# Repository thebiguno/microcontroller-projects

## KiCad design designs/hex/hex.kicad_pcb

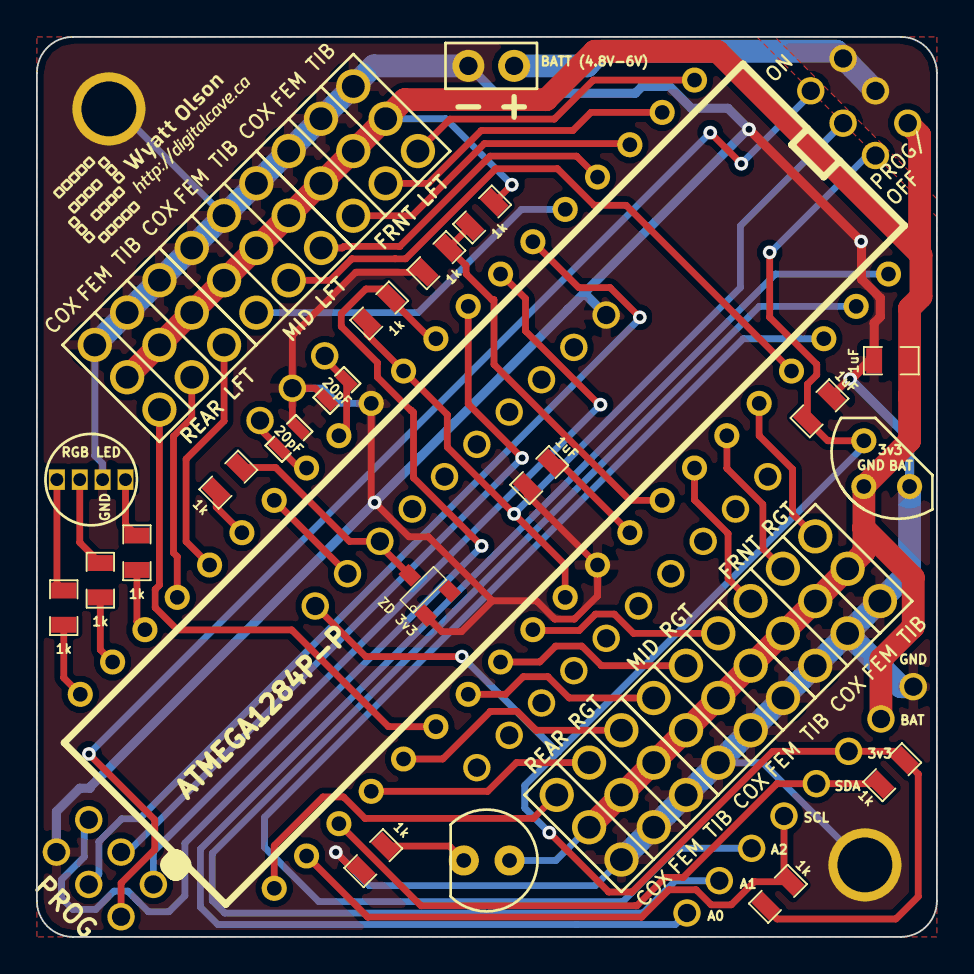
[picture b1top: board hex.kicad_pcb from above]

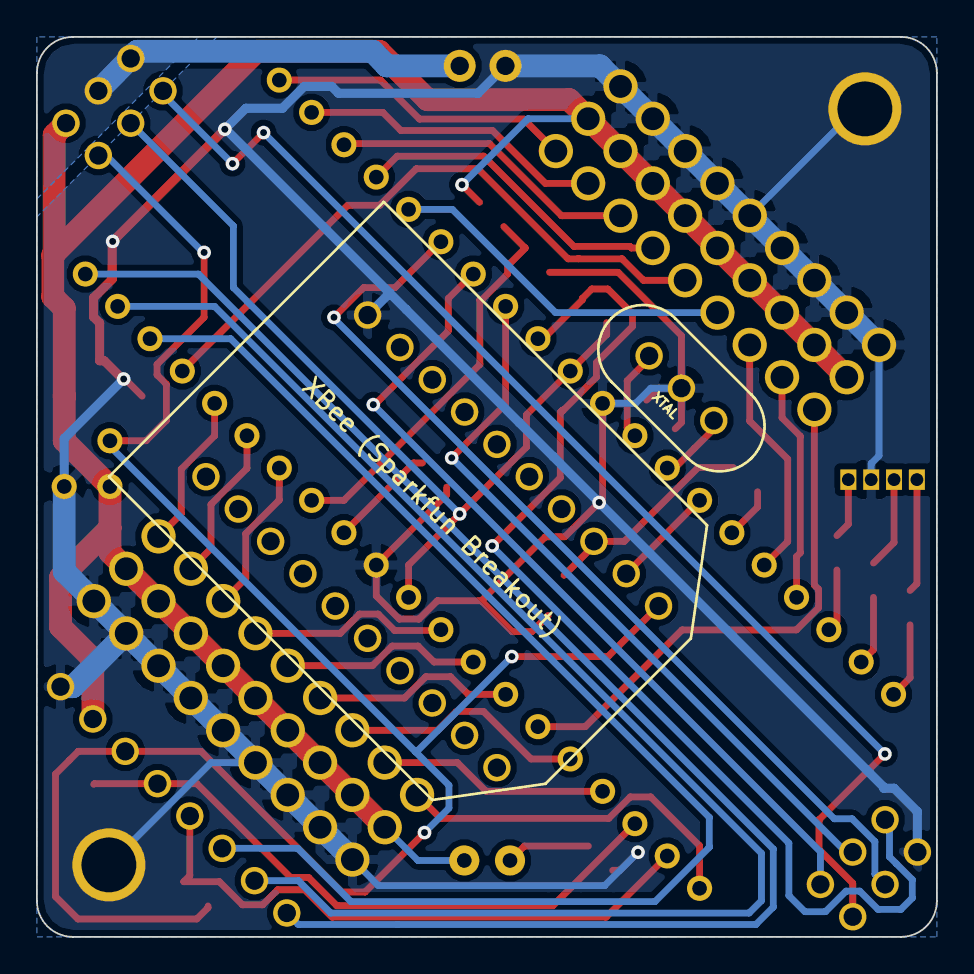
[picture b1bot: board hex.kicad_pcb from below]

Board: 2 copper layers, 50.0 x 50.0 mm, 35 parts (2 on the bottom side), 47 nets.

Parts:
1PIN, 1PIN#2: P***; 1pin
C1, C2, C3: 1uF; SM0805
C4, C5: 20pF; SM0603_Capa
D1: LED; LED-5MM
IC1: ATMEGA1284P-P; DIP-40__600
K1: XTAL; PIN_ARRAY_3X1
K2: REGUL; TO92
L1: RGB LED; LED_RGB
P1: PROG; pin_array_3x2
P2: BATT (4.8V-6V); PIN_ARRAY_2X1
P3: CONN_8; PIN_ARRAY_8x1
R1, R2, R3, R4, R5, R6, R7, R8, R9, R10: 1k; SM0805
S1: FRNT LFT; HEX_LEG
S2: FRNT RGT; HEX_LEG_REVERSE
S3: MID LFT; HEX_LEG
S4: MID RGT; HEX_LEG_REVERSE
S5: REAR LFT; HEX_LEG
S6: REAR RGT; HEX_LEG_REVERSE
SW1: DPDT
VAL: DIGITALCAVE_LOGO_WIDE_SMALL
X1: XBee (Sparkfun Breakout); XBEE_SPARKFUN_BREAKOUT
ZD1: ZD 3v3; SOT23

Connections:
ADC0: IC1.40, P3.1
ADC1: IC1.39, P3.2
ADC2: IC1.38, P3.3
ADC_BATTERY_METER: IC1.33, R2.2, R3.2
AREF: C1.2, IC1.32
AVR_RX: IC1.14, X1.2
AVR_TX: R9.2, X1.3, ZD1.2
BATTERY: P2.1, SW1.1, SW1.2
GND: 1PIN.1, 1PIN#2.1, C1.1, C2.1, C3.2, C4.1, C5.1, IC1.11, IC1.31, K1.2, K2.1, L1.2, P1.6, P2.2, P3.8, R3.1, R10.2, S1.7, S1.8, S1.9, S2.7, S2.8, S2.9, S3.7, S3.8, S3.9, S4.7, S4.8, S4.9, S5.7, S5.8, S5.9, S6.7, S6.8, S6.9, X1.10, ZD1.1
I2C_SCL: IC1.22, P3.4, R8.2
I2C_SDA: IC1.23, P3.5, R7.2
LED_BLUE: IC1.19, R6.1
LED_BLUE_R: L1.3, R6.2
LED_GREEN: IC1.20, R5.1
LED_GREEN_R: L1.4, R5.2
LED_RED: IC1.18, R4.1
LED_RED_R: L1.1, R4.2
MISO: IC1.7, P1.1
MOSI: IC1.6, P1.4
unnamed: D1.2, R10.1
unnamed: IC1.15, R9.1
PWM00: IC1.3, S1.1
PWM01: IC1.2, S1.2
PWM02: IC1.1, S1.3
PWM03: IC1.36, S2.1
PWM04: IC1.35, S2.2
PWM05: IC1.34, S2.3
PWM06: IC1.5, S3.1
PWM07: IC1.37, S3.2
PWM08: IC1.4, S3.3
PWM09: IC1.29, S4.1
PWM10: IC1.28, S4.2
PWM11: IC1.27, S4.3
PWM12: IC1.26, S5.1
PWM13: IC1.17, S5.2
PWM14: IC1.16, S5.3
PWM15: IC1.25, S6.1
PWM16: IC1.24, S6.2
PWM17: IC1.21, S6.3
RESET: IC1.9, P1.5, R1.1
SCK: IC1.8, P1.3
SWITCHED_BATTERY: C2.2, D1.1, K2.2, P3.7, R2.1, S1.4, S1.5, S1.6, S2.4, S2.5, S2.6, S3.4, S3.5, S3.6, S4.4, S4.5, S4.6, S5.4, S5.5, S5.6, S6.4, S6.5, S6.6, SW1.3
VCC_3v3: C3.1, K2.3, P3.6, R7.1, R8.1, SW1.6, X1.1
VCC_AVR: IC1.10, IC1.30, R1.2, SW1.5
VCC_PROG: P1.2, SW1.4
XTAL1: C5.2, IC1.13, K1.1
XTAL2: C4.2, IC1.12, K1.3

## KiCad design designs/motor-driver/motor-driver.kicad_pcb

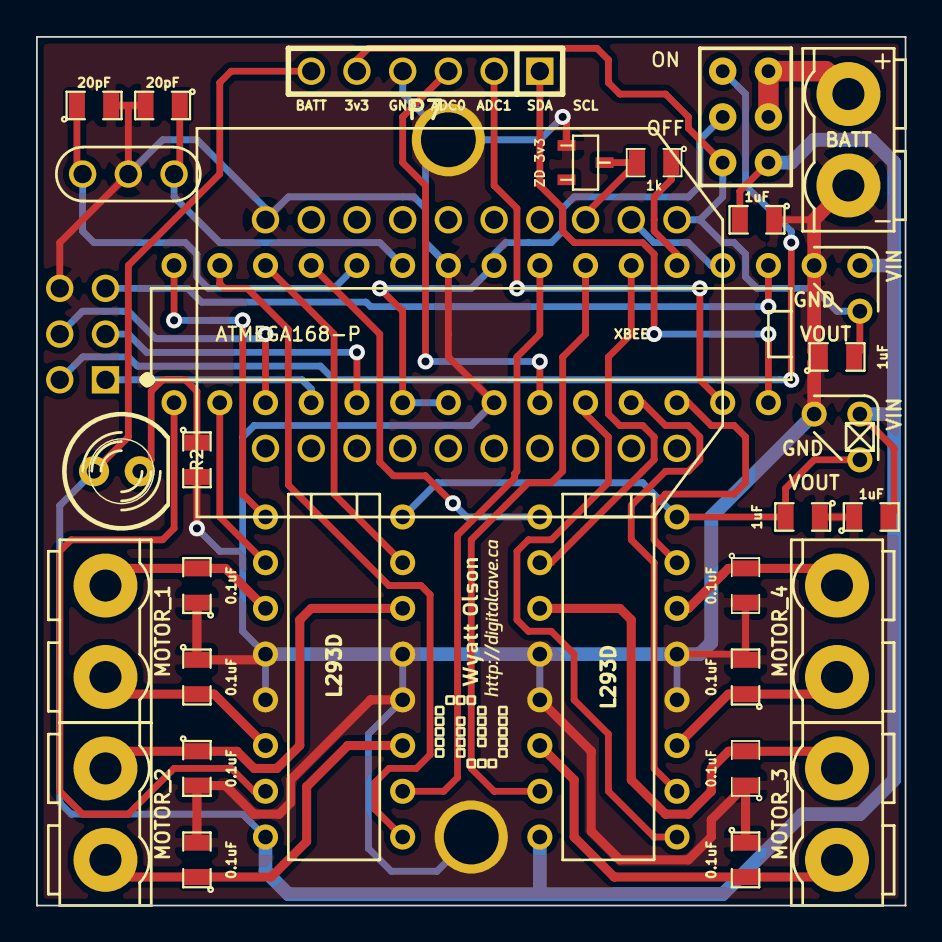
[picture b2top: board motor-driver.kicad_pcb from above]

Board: 2 copper layers, 48.3 x 48.3 mm, 36 parts (0 on the bottom side), 40 nets.

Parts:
1PIN, 1PIN#2: P***; 1pin
C1, C2, C3, C4: 1uF; SM0805
C5, C6: 20pF; SM0805
C7, C8, C9, C10, C11, C12, C13, C14: 0.1uF; SM0805
D1: ZD 3v3; sot23
D2: LED; LED-5MM
IC1: ATMEGA168-P; DIP-28__300
P1: BATT; SCREW_TERMINAL_2
P2: ISP
P3: MOTOR_1; SCREW_TERMINAL_2
P4: MOTOR_2; SCREW_TERMINAL_2
P5: MOTOR_3; SCREW_TERMINAL_2
P6: MOTOR_4; SCREW_TERMINAL_2
P7: CONN_6; PIN_ARRAY-6X1
R1, R2: 1k; SM0805
S1: DPDT
U1, U2: L293D; DIP-16__300
VAL: DIGITALCAVE_LOGO_WIDE_SMALL
VR1, VR2: MCP1702; TO92_SMALL
X1: CRYSTAL_RESONATOR
X2: XBEE; XBEE_SPARKFUN_BREAKOUT

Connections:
+3.3V: C4.2, P7.5, S1.6, VR2.3, X2.1
+5V: C2.2, U1.16, U2.16, VR1.3
+BATT: C1.2, C3.2, D2.1, P7.6, S1.3, U1.8, U2.8, VR1.2, VR2.2
/ADC0: IC1.23, P7.3
/AVR_VCC: IC1.7, IC1.20, IC1.21, S1.5
/BATTERY: P1.2, S1.1, S1.2
/MISO: IC1.18, P2.1
/MOSI: IC1.17, P2.4
/MOTOR1_1A: IC1.16, U1.2
/MOTOR1_1Y: C7.2, P3.1, U1.3
/MOTOR1_2A: IC1.15, U1.7
/MOTOR1_2Y: C11.2, P3.2, U1.6
/MOTOR1_ENABLE: IC1.14, U1.1
/MOTOR2_3A: IC1.6, U1.10
/MOTOR2_3Y: C12.1, P4.2, U1.11
/MOTOR2_4A: IC1.12, U1.15
/MOTOR2_4Y: C8.1, P4.1, U1.14
/MOTOR2_ENABLE: IC1.13, U1.9
/MOTOR3_1A: IC1.4, U2.2
/MOTOR3_1Y: C9.2, P5.2, U2.3
/MOTOR3_2A: IC1.5, U2.7
/MOTOR3_2Y: C13.2, P5.1, U2.6
/MOTOR3_ENABLE: IC1.11, U2.1
/MOTOR4_3A: IC1.25, U2.10
/MOTOR4_3Y: C14.1, P6.1, U2.11
/MOTOR4_4A: IC1.26, U2.15
/MOTOR4_4Y: C10.1, P6.2, U2.14
/MOTOR4_ENABLE: IC1.24, U2.9
/PROG_VCC: P2.2, S1.4
/RESET: IC1.1, P2.5
/RX: IC1.2, X2.2
/SCK: IC1.19, P2.3
/SCL: IC1.28, P7.1
/SDA: IC1.27, P7.2
/TX: IC1.3, R1.1
/XTAL1: C5.1, IC1.9, X1.1
/XTAL2: C6.1, IC1.10, X1.2
GND: 1PIN.1, 1PIN#2.1, C1.1, C2.1, C3.1, C4.1, C5.2, C6.2, C7.1, C8.2, C9.1, C10.2, C11.1, C12.2, C13.1, C14.2, D1.1, IC1.8, IC1.22, P1.1, P2.6, P7.4, R2.2, U1.4, U1.5, U1.12, U1.13, U2.4, U2.5, U2.12, U2.13, VR1.1, VR2.1, X1.3, X2.10
unnamed: D2.2, R2.1
unnamed: D1.2, R1.2, X2.3

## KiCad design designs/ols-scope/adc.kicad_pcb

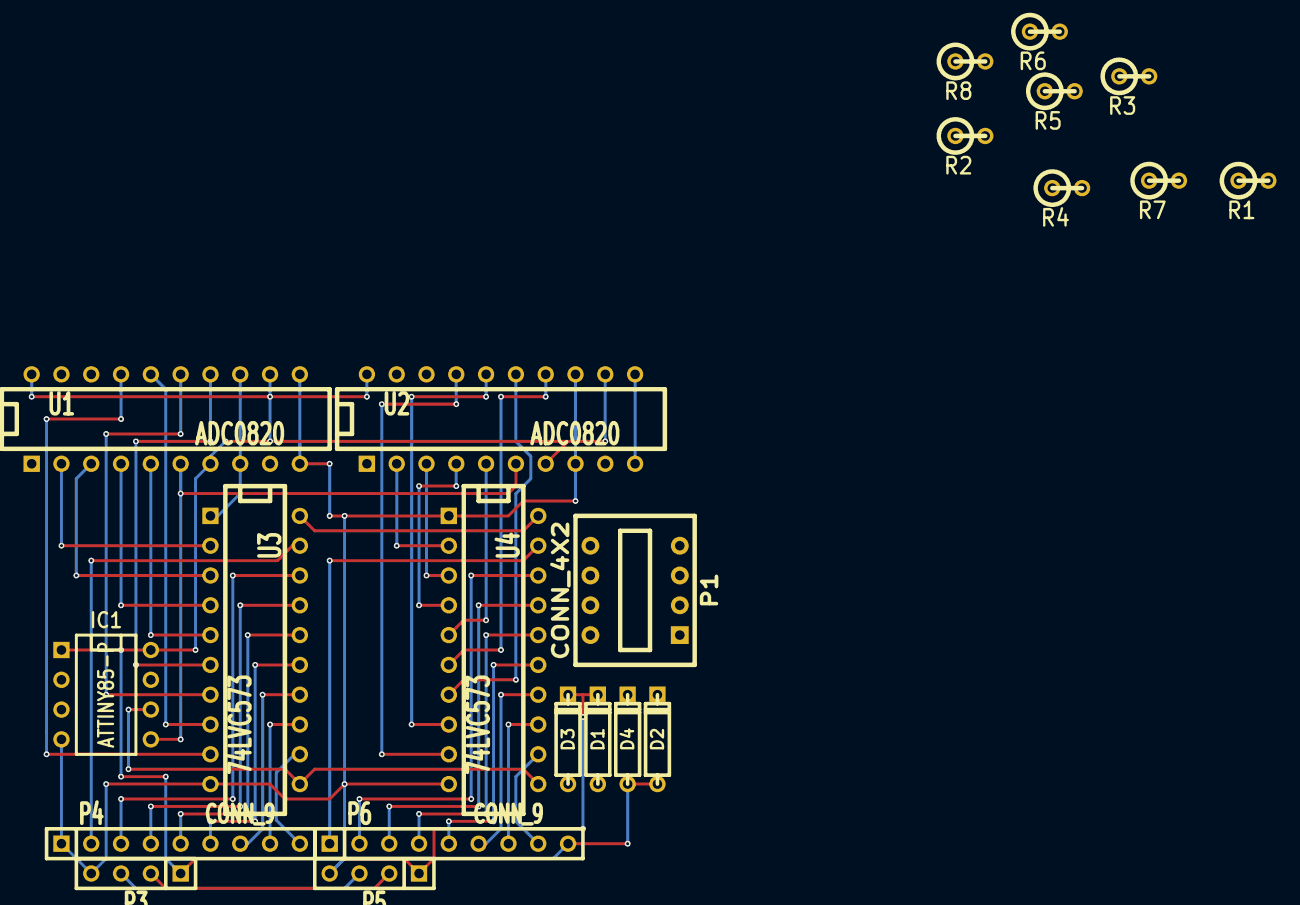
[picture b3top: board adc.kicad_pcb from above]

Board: 2 copper layers, 22 parts (0 on the bottom side), 47 nets.

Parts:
D1, D2, D3, D4: DIODESCH; D3
IC1: ATTINY85-P; DIP-8__300
P1: CONN_4X2; SWDIP4
P3, P5: CONN_4; SIL-4
P4, P6: CONN_9; SIL-9
R1, R2: 1k; R1
R3, R5: 10k; R1
R4, R6: 2k; R1
R7, R8: 100k; R1
U1, U2: ADC0820; DIP-20__300
U3, U4: 74LVC573; DIP-20__300

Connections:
+2.5V: P3.3, P5.3
+3.3V: P3.2, P5.2
+5V: D1.2, D3.2, IC1.1, IC1.8, P3.1, P5.1, U1.7, U1.12, U1.20, U2.7, U2.12, U2.20
ANALOG_IN_1: P1.1, R3.1
ANALOG_IN_2: P1.5, R5.1
Channel 16: P4.2, U3.19
Channel 17: P4.3, U3.18
Channel 18: P4.4, U3.17
Channel 19: P4.5, U3.16
Channel 20: P4.6, U3.15
Channel 21: P4.7, U3.14
Channel 22: P4.8, U3.13
Channel 23: P4.9, U3.12
Channel 24: P6.1, U4.19
Channel 25: P6.2, U4.18
Channel 26: P6.3, U4.17
Channel 27: P6.4, U4.16
Channel 28: P6.5, U4.15
Channel 29: P6.6, U4.14
Channel 30: P6.7, U4.13
Channel 31: P6.8, U4.12
DIP_1B: P1.2, P1.4, R3.2, R4.1
DIP_2A: P1.3, R1.1, R4.2, R7.1
DIP_3B: P1.6, P1.8, R5.2, R6.1
DIP_4A: P1.7, R2.1, R6.2, R8.1
GND: D2.1, D4.1, IC1.4, P3.4, P4.1, P5.4, P6.9, R1.2, R2.2, U1.8, U1.10, U1.11, U1.13, U2.8, U2.10, U2.11, U2.13, U3.1, U3.10, U4.1, U4.10
unnamed: U2.17, U4.9
unnamed: U2.16, U4.8
unnamed: U2.15, U4.7
unnamed: U2.14, U4.6
unnamed: U2.5, U4.5
unnamed: U2.4, U4.4
unnamed: U2.3, U4.3
unnamed: U2.2, U4.2
unnamed: IC1.5, U1.6, U2.6
unnamed: IC1.6, U3.11, U4.11
unnamed: U1.3, U3.3
unnamed: U1.2, U3.2
unnamed: D1.1, D2.2, R7.2, U1.1
unnamed: U1.16, U3.8
unnamed: U1.17, U3.9
unnamed: U1.15, U3.7
unnamed: U1.14, U3.6
unnamed: U1.5, U3.5
unnamed: U1.4, U3.4
unnamed: D3.1, D4.2, R8.2, U2.1
VCC: U3.20, U4.20

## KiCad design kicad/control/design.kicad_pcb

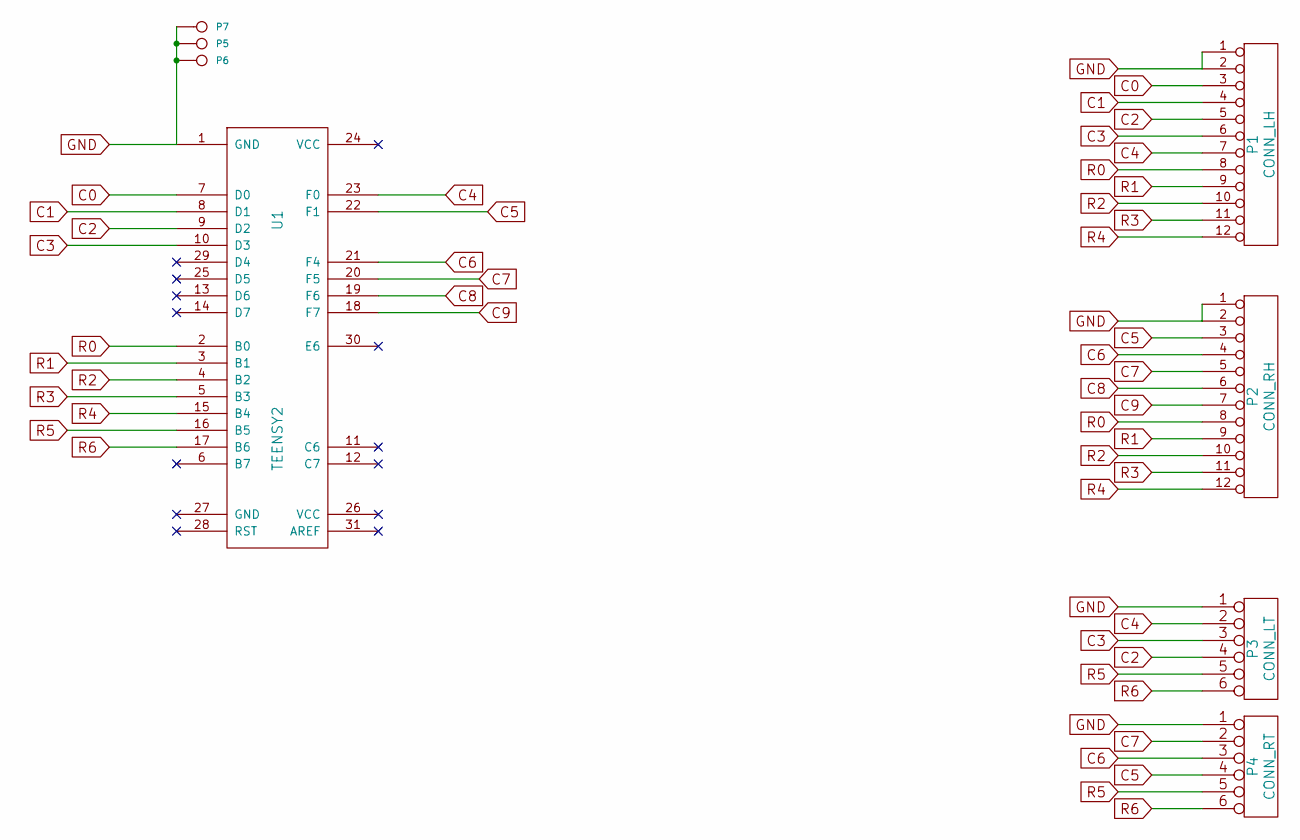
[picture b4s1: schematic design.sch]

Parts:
P1: CONN_LH
P2: CONN_RH
P3: CONN_LT
P4: CONN_RT
P5, P6, P7: CONN_1
U1: TEENSY2

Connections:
C0: P1.3, U1.7 (D0)
C1: P1.4, U1.8 (D1)
C2: P1.5, P3.4, U1.9 (D2)
C3: P1.6, P3.3, U1.10 (D3)
C4: P1.7, P3.2, U1.23 (F0)
C5: P2.3, P4.4, U1.22 (F1)
C6: P2.4, P4.3, U1.21 (F4)
C7: P2.5, P4.2, U1.20 (F5)
C8: P2.6, U1.19 (F6)
C9: P2.7, U1.18 (F7)
GND: P1.1, P1.2, P2.1, P2.2, P3.1, P4.1, P5.1, P6.1, P7.1, U1.1 (GND)
R0: P1.8, P2.8, U1.2 (B0)
R1: P1.9, P2.9, U1.3 (B1)
R2: P1.10, P2.10, U1.4 (B2)
R3: P1.11, P2.11, U1.5 (B3)
R4: P1.12, P2.12, U1.15 (B4)
R5: P3.5, P4.5, U1.16 (B5)
R6: P3.6, P4.6, U1.17 (B6)

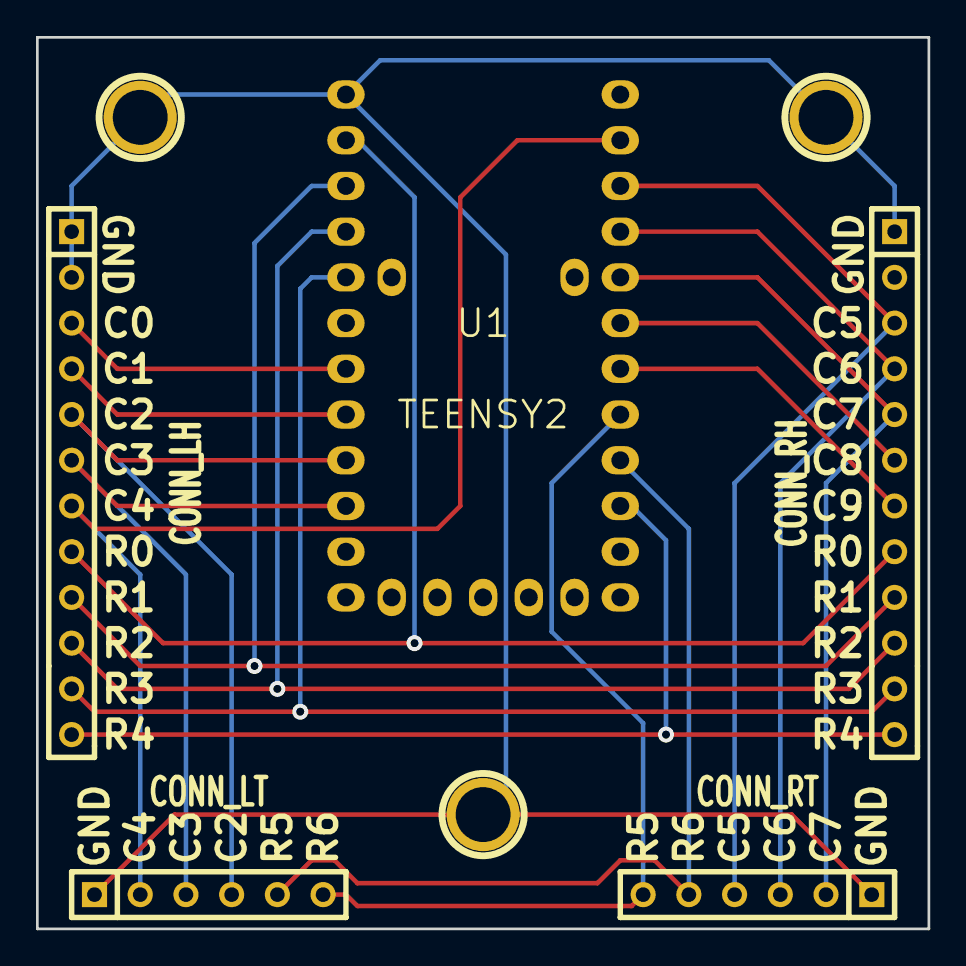
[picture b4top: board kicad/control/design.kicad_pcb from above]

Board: 2 copper layers, 49.5 x 49.5 mm, 8 parts (0 on the bottom side), 18 nets.

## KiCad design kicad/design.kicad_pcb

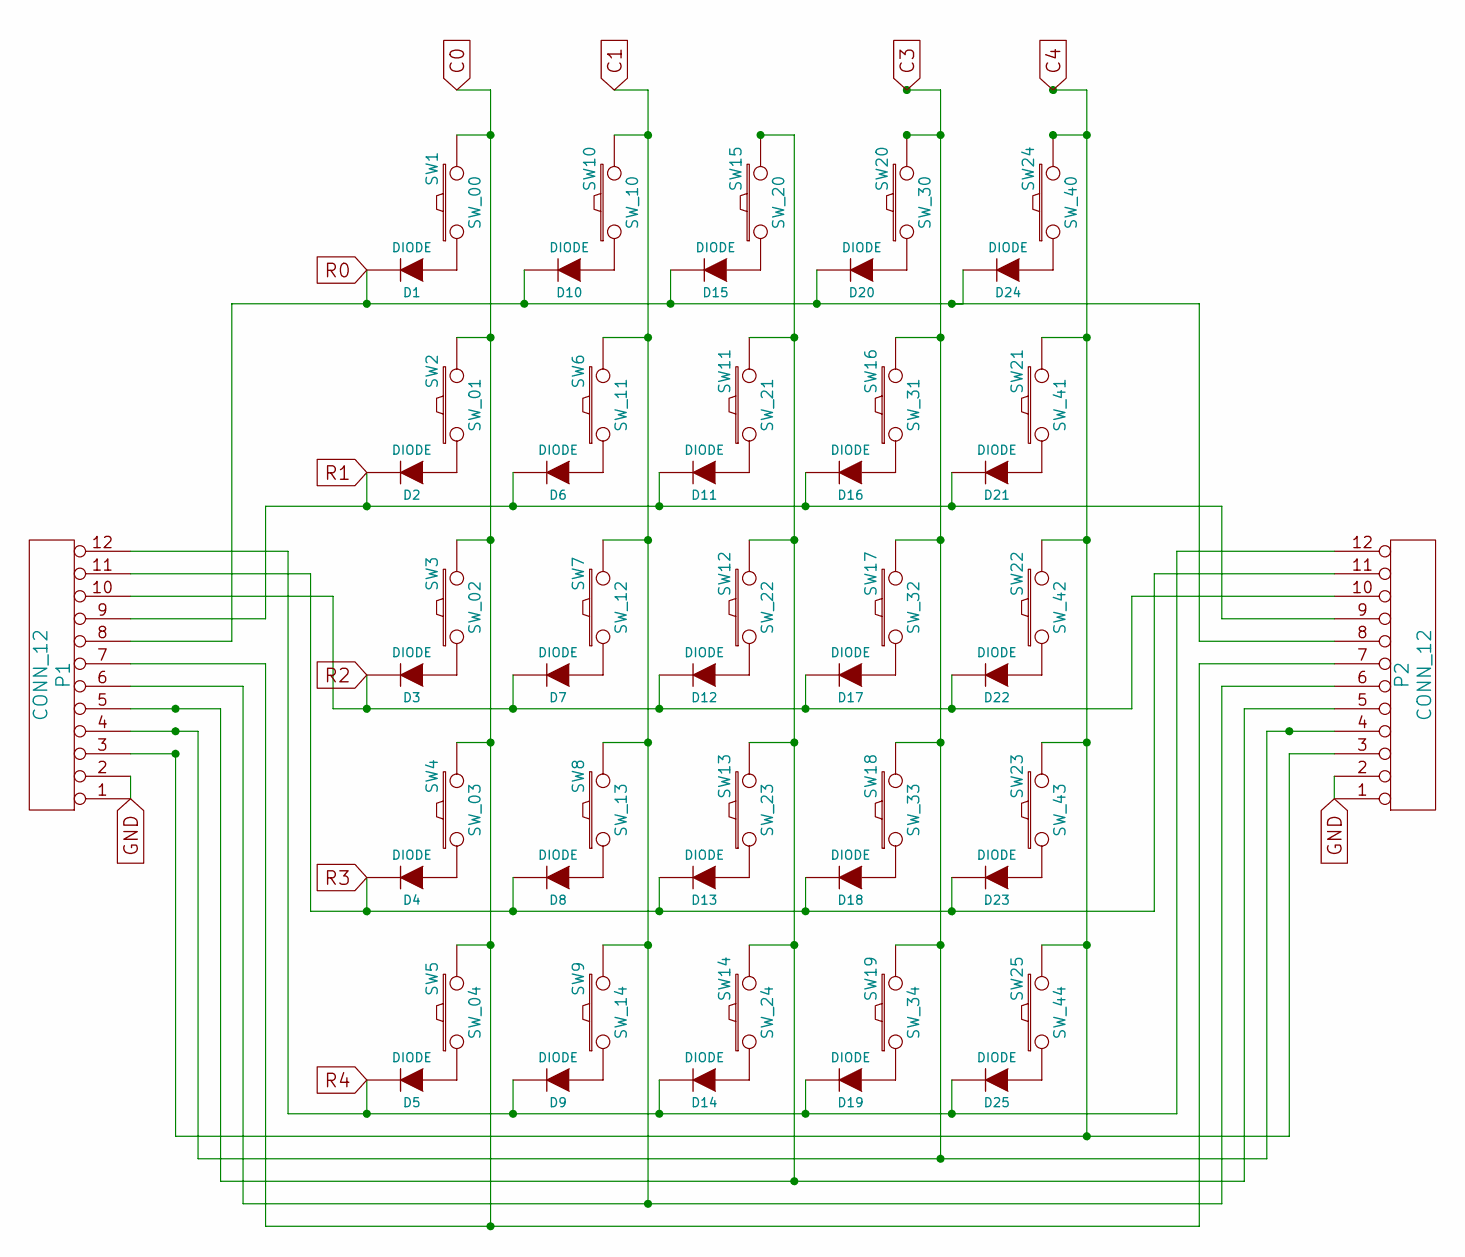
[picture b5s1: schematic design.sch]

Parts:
D1, D2, D3, D4, D5, D6, D7, D8, D9, D10, D11, D12, D13, D14, D15, D16, D17, D18, D19, D20, D21, D22, D23, D24, D25: DIODE
P1, P2: CONN_12
SW1: SW_00
SW2: SW_01
SW3: SW_02
SW4: SW_03
SW5: SW_04
SW6: SW_11
SW7: SW_12
SW8: SW_13
SW9: SW_14
SW10: SW_10
SW11: SW_21
SW12: SW_22
SW13: SW_23
SW14: SW_24
SW15: SW_20
SW16: SW_31
SW17: SW_32
SW18: SW_33
SW19: SW_34
SW20: SW_30
SW21: SW_41
SW22: SW_42
SW23: SW_43
SW24: SW_40
SW25: SW_44

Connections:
C0: P1.7, P2.7, SW1.2, SW2.2, SW3.2, SW4.2, SW5.2
C1: P1.6, P2.6, SW6.2, SW7.2, SW8.2, SW9.2, SW10.2
C3: P1.4, P2.4, SW16.2, SW17.2, SW18.2, SW19.2, SW20.2
C4: P1.3, P2.3, SW21.2, SW22.2, SW23.2, SW24.2, SW25.2
GND: P1.1, P1.2, P2.1, P2.2
unnamed: D17.1 (A), SW17.1
unnamed: D12.1 (A), SW12.1
unnamed: D7.1 (A), SW7.1
unnamed: D3.1 (A), SW3.1
unnamed: D21.1 (A), SW21.1
unnamed: D18.1 (A), SW18.1
unnamed: D13.1 (A), SW13.1
unnamed: D8.1 (A), SW8.1
unnamed: D4.1 (A), SW4.1
unnamed: D22.1 (A), SW22.1
unnamed: D20.1 (A), SW20.1
unnamed: D15.1 (A), SW15.1
unnamed: D24.1 (A), SW24.1
unnamed: D10.1 (A), SW10.1
unnamed: D1.1 (A), SW1.1
unnamed: D16.1 (A), SW16.1
unnamed: D11.1 (A), SW11.1
unnamed: P1.5, P2.5, SW11.2, SW12.2, SW13.2, SW14.2, SW15.2
unnamed: D6.1 (A), SW6.1
unnamed: D2.1 (A), SW2.1
unnamed: D14.1 (A), SW14.1
unnamed: D9.1 (A), SW9.1
unnamed: D5.1 (A), SW5.1
unnamed: D23.1 (A), SW23.1
unnamed: D25.1 (A), SW25.1
unnamed: D19.1 (A), SW19.1
R0: D1.2 (K), D10.2 (K), D15.2 (K), D20.2 (K), D24.2 (K), P1.8, P2.8
R1: D2.2 (K), D6.2 (K), D11.2 (K), D16.2 (K), D21.2 (K), P1.9, P2.9
R2: D3.2 (K), D7.2 (K), D12.2 (K), D17.2 (K), D22.2 (K), P1.10, P2.10
R3: D4.2 (K), D8.2 (K), D13.2 (K), D18.2 (K), D23.2 (K), P1.11, P2.11
R4: D5.2 (K), D9.2 (K), D14.2 (K), D19.2 (K), D25.2 (K), P1.12, P2.12

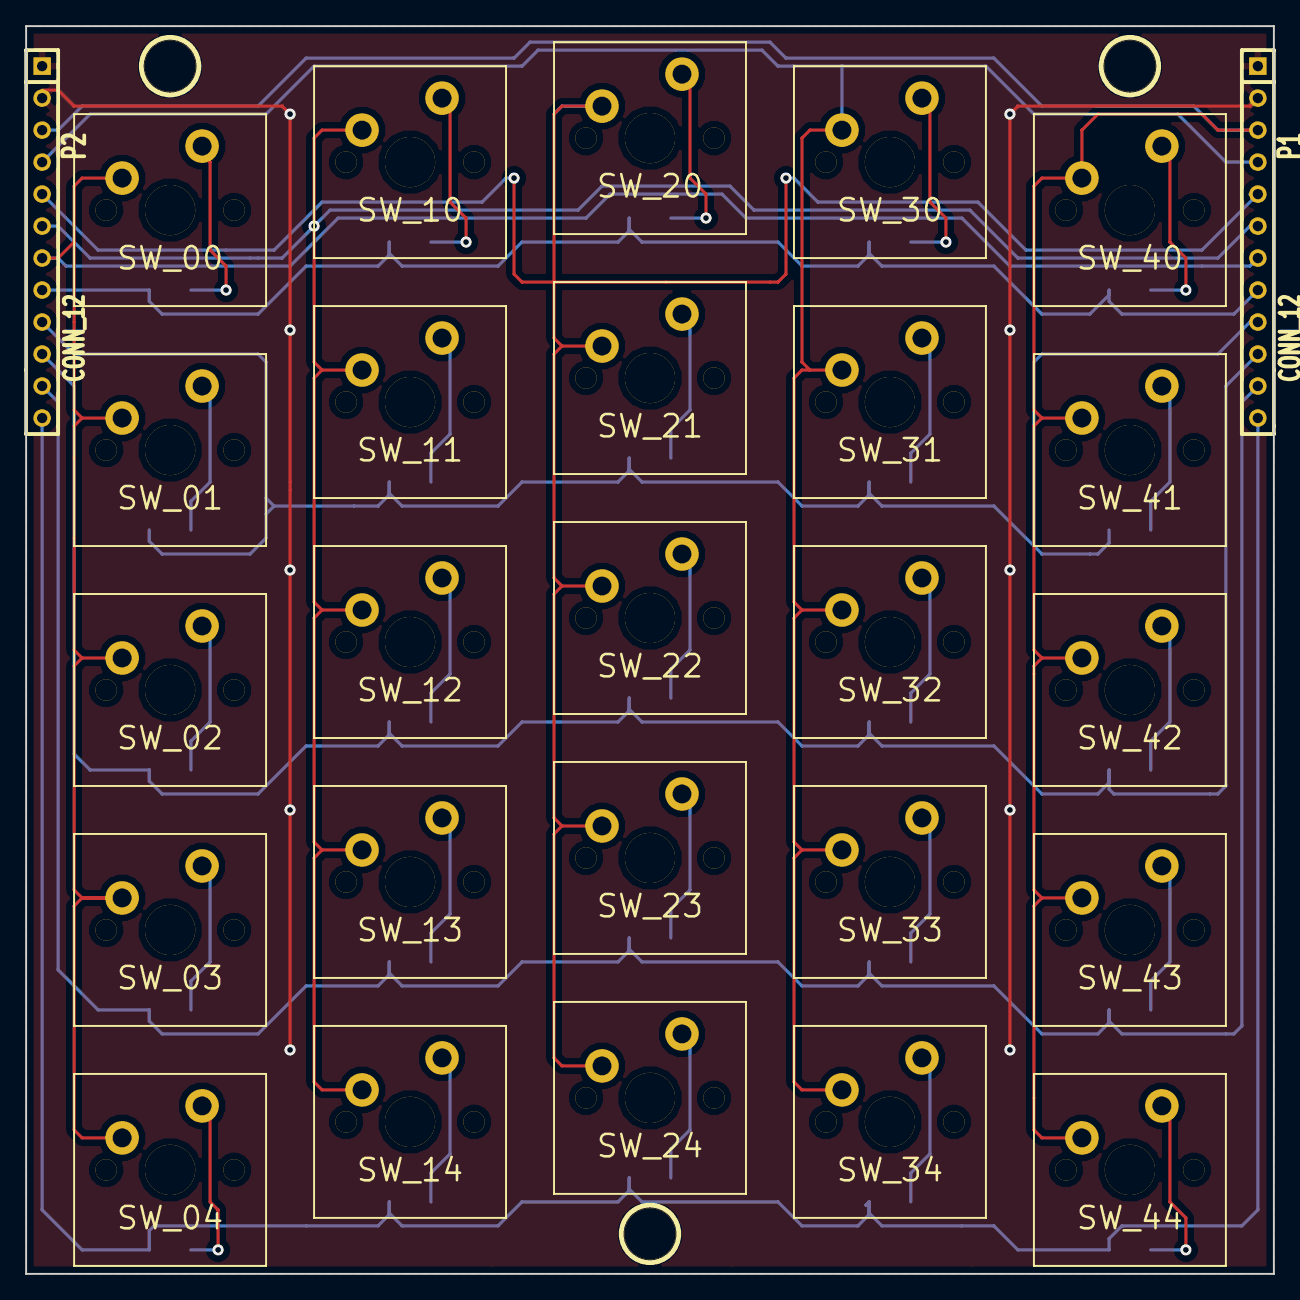
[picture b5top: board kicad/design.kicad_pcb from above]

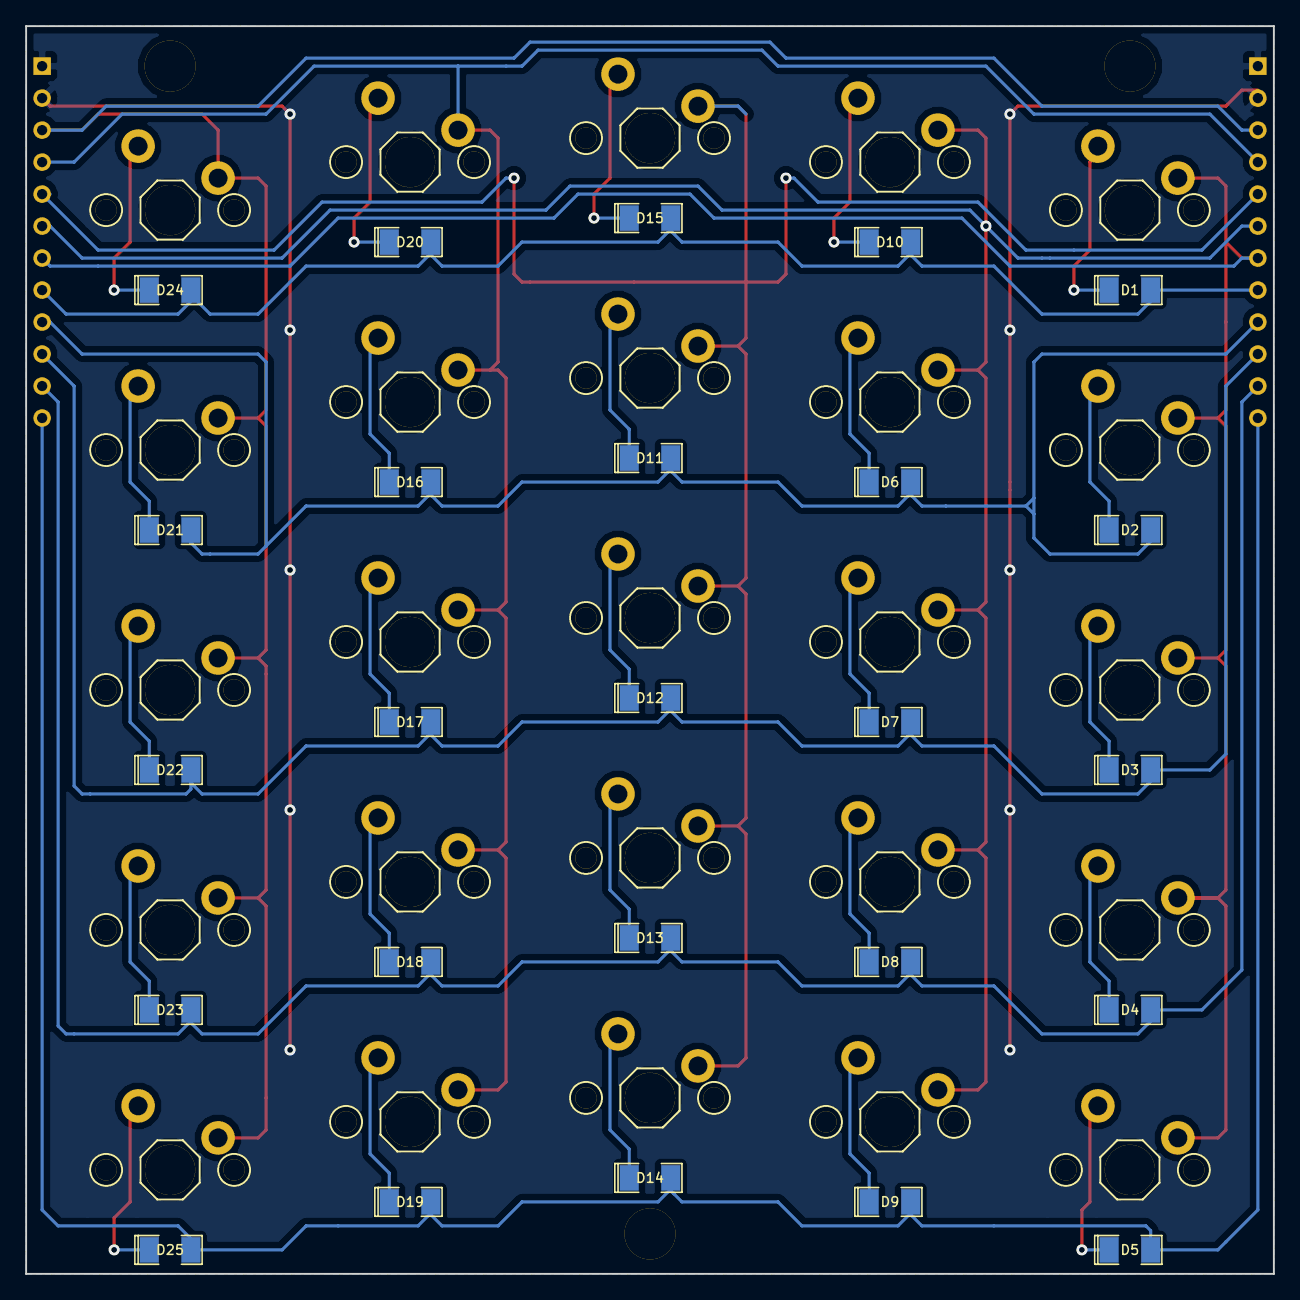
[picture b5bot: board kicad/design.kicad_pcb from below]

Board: 2 copper layers, 99.1 x 99.1 mm, 55 parts (25 on the bottom side), 36 nets.

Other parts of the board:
1PIN, 1PIN#2, 1PIN#3: P***; 1pin
